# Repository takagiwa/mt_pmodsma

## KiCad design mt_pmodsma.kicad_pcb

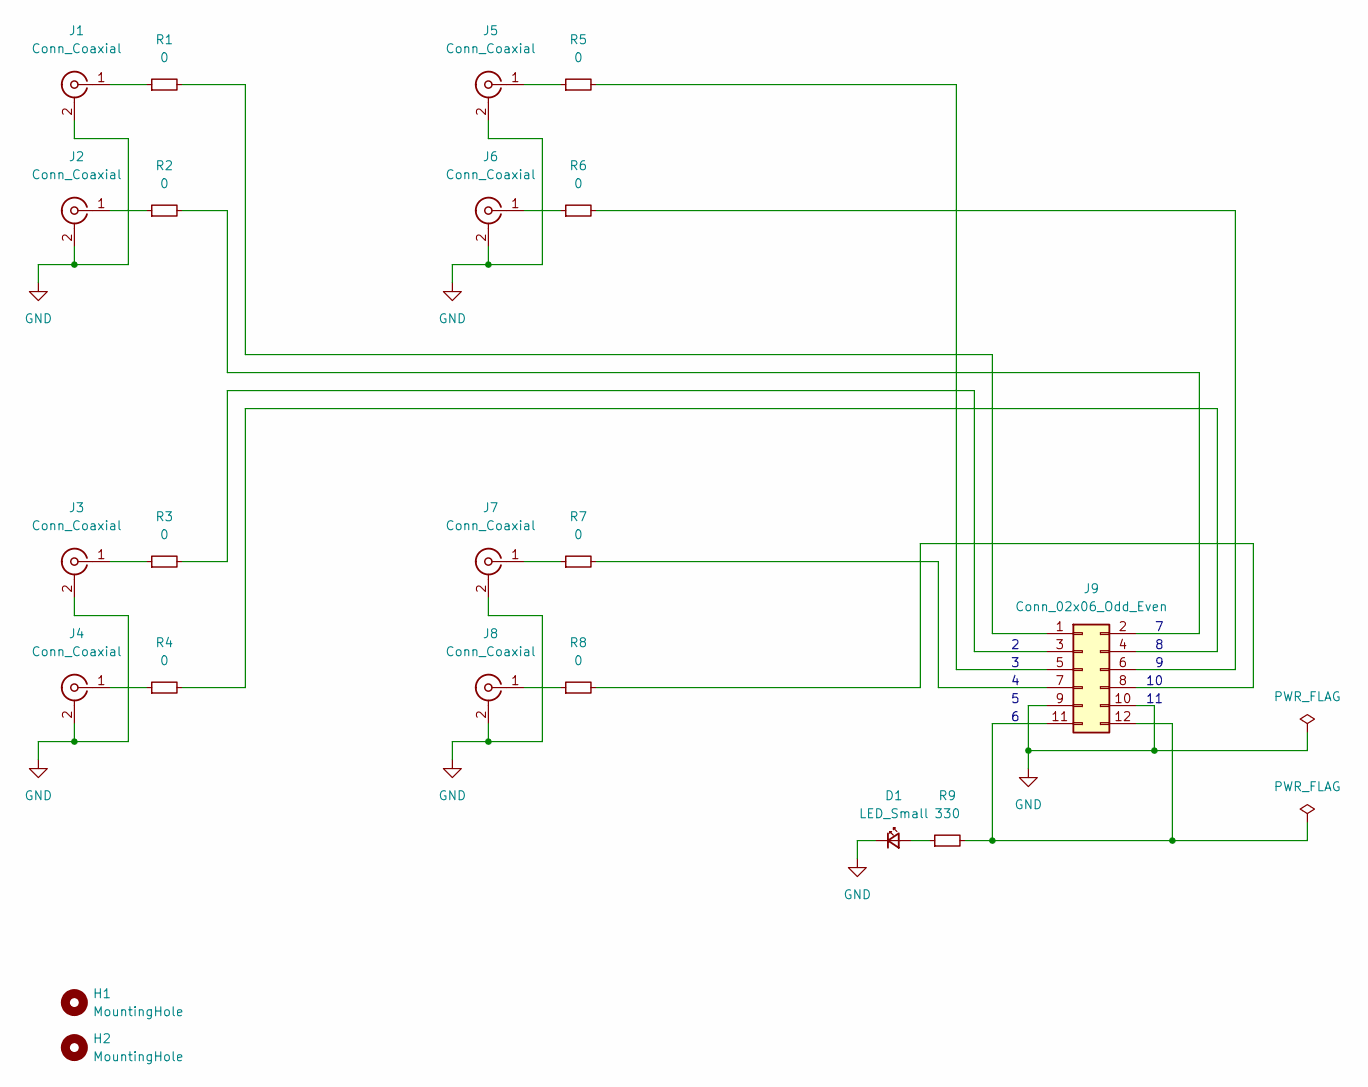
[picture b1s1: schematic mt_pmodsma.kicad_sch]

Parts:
D1: LED_Small; LED_0805_2012Metric_Pad1.15x1.40mm_HandSolder
H1, H2: MountingHole; MountingHole_3.2mm_M3
J1, J2, J3, J4, J5, J6, J7, J8: Conn_Coaxial; SMA_Amphenol_901-144_Vertical
J9: Conn_02x06_Odd_Even; PinSocket_2x06_P2.54mm_Vertical
R1, R2, R3, R4, R5, R6, R7, R8: 0; R_0805_2012Metric_Pad1.20x1.40mm_HandSolder
R9: 330; R_0805_2012Metric_Pad1.20x1.40mm_HandSolder

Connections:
GND: D1.1 (K), J1.2 (Ext), J2.2 (Ext), J3.2 (Ext), J4.2 (Ext), J5.2 (Ext), J6.2 (Ext), J7.2 (Ext), J8.2 (Ext), J9.9, J9.10
unnamed: D1.2 (A), R9.1
unnamed: J1.1 (In), R1.1
unnamed: J2.1 (In), R2.1
unnamed: J3.1 (In), R3.1
unnamed: J4.1 (In), R4.1
unnamed: J5.1 (In), R5.1
unnamed: J6.1 (In), R6.1
unnamed: J7.1 (In), R7.1
unnamed: J8.1 (In), R8.1
unnamed: J9.1, R1.2
unnamed: J9.2, R2.2
unnamed: J9.3, R3.2
unnamed: J9.4, R4.2
unnamed: J9.5, R5.2
unnamed: J9.6, R6.2
unnamed: J9.7, R7.2
unnamed: J9.8, R8.2
unnamed: J9.11, J9.12, R9.2

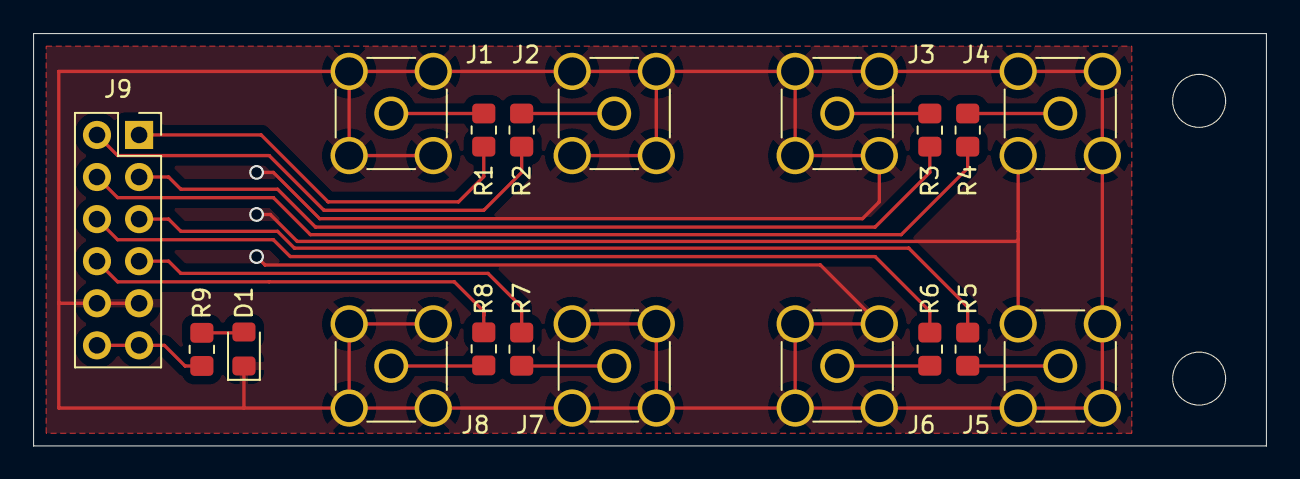
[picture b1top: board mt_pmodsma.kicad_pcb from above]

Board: 2 copper layers, 74.4 x 24.9 mm, 21 parts (0 on the bottom side), 19 nets.

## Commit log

2022-07-24 Initial design
2022-07-30 first gerber
